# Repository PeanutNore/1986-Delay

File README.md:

# 1986-Delay
This program is distributed in the hope that it will be useful,
but WITHOUT ANY WARRANTY; without even the implied warranty of
MERCHANTABILITY or FITNESS FOR A PARTICULAR PURPOSE.

1986 Delay: A Stereo Digital Delay pedal for guitar built around the AVR128DA28 MCU.

Up to 1000 millisecond delay with stereo outputs and two modes

Mode 1: Ping-Pong delay. Output B has half the delay time of output A

Mode 2: "Reverse Ping-Pong" delay. Output A has half the selected delay time and runs like a stardard delay, while output B runs in reverse and is synchronized with output A for a stereo effect.

Digital Controls:

  A: Effective delay line length
  
  B: Sample rate

Analog Controls:

  Mix: The amount of delayed signal mixed with the dry signal at output
  
  Feedback: The amount of delayed signal mixed with the input signal to the delay line

 * Copyright 2025 Samuel Brown. All Rights Reservered.
 * 
 * Licensed under Creative Commons CC-BY-NC-SA 4.0
 * https://creativecommons.org/licenses/by-nc-sa/4.0/
 * 
 * You are free to share and adapt this software for non-
 * commercial purposes provided that you give appropriate 
 * credit and attribution, and distribute your contributions 
 * under the same CC-BY-NC-SA license.
 * 
 * For commercial licensing contact sam.brown.rit08@gmail.com

To use this software you will need:
* Arduino IDE version 1.8.19 or greater
* DxCore library for AVR128DA28 support (https://github.com/SpenceKonde/DxCore)
* Any USB to UPDI programmer. I recommend the Adafruit UPDI Friend because it is easy to use and under $20
* An AVR128DA28 MCU and appropriate supporting circuitry. Refer to the KiCad schematic and board files included in this repository.

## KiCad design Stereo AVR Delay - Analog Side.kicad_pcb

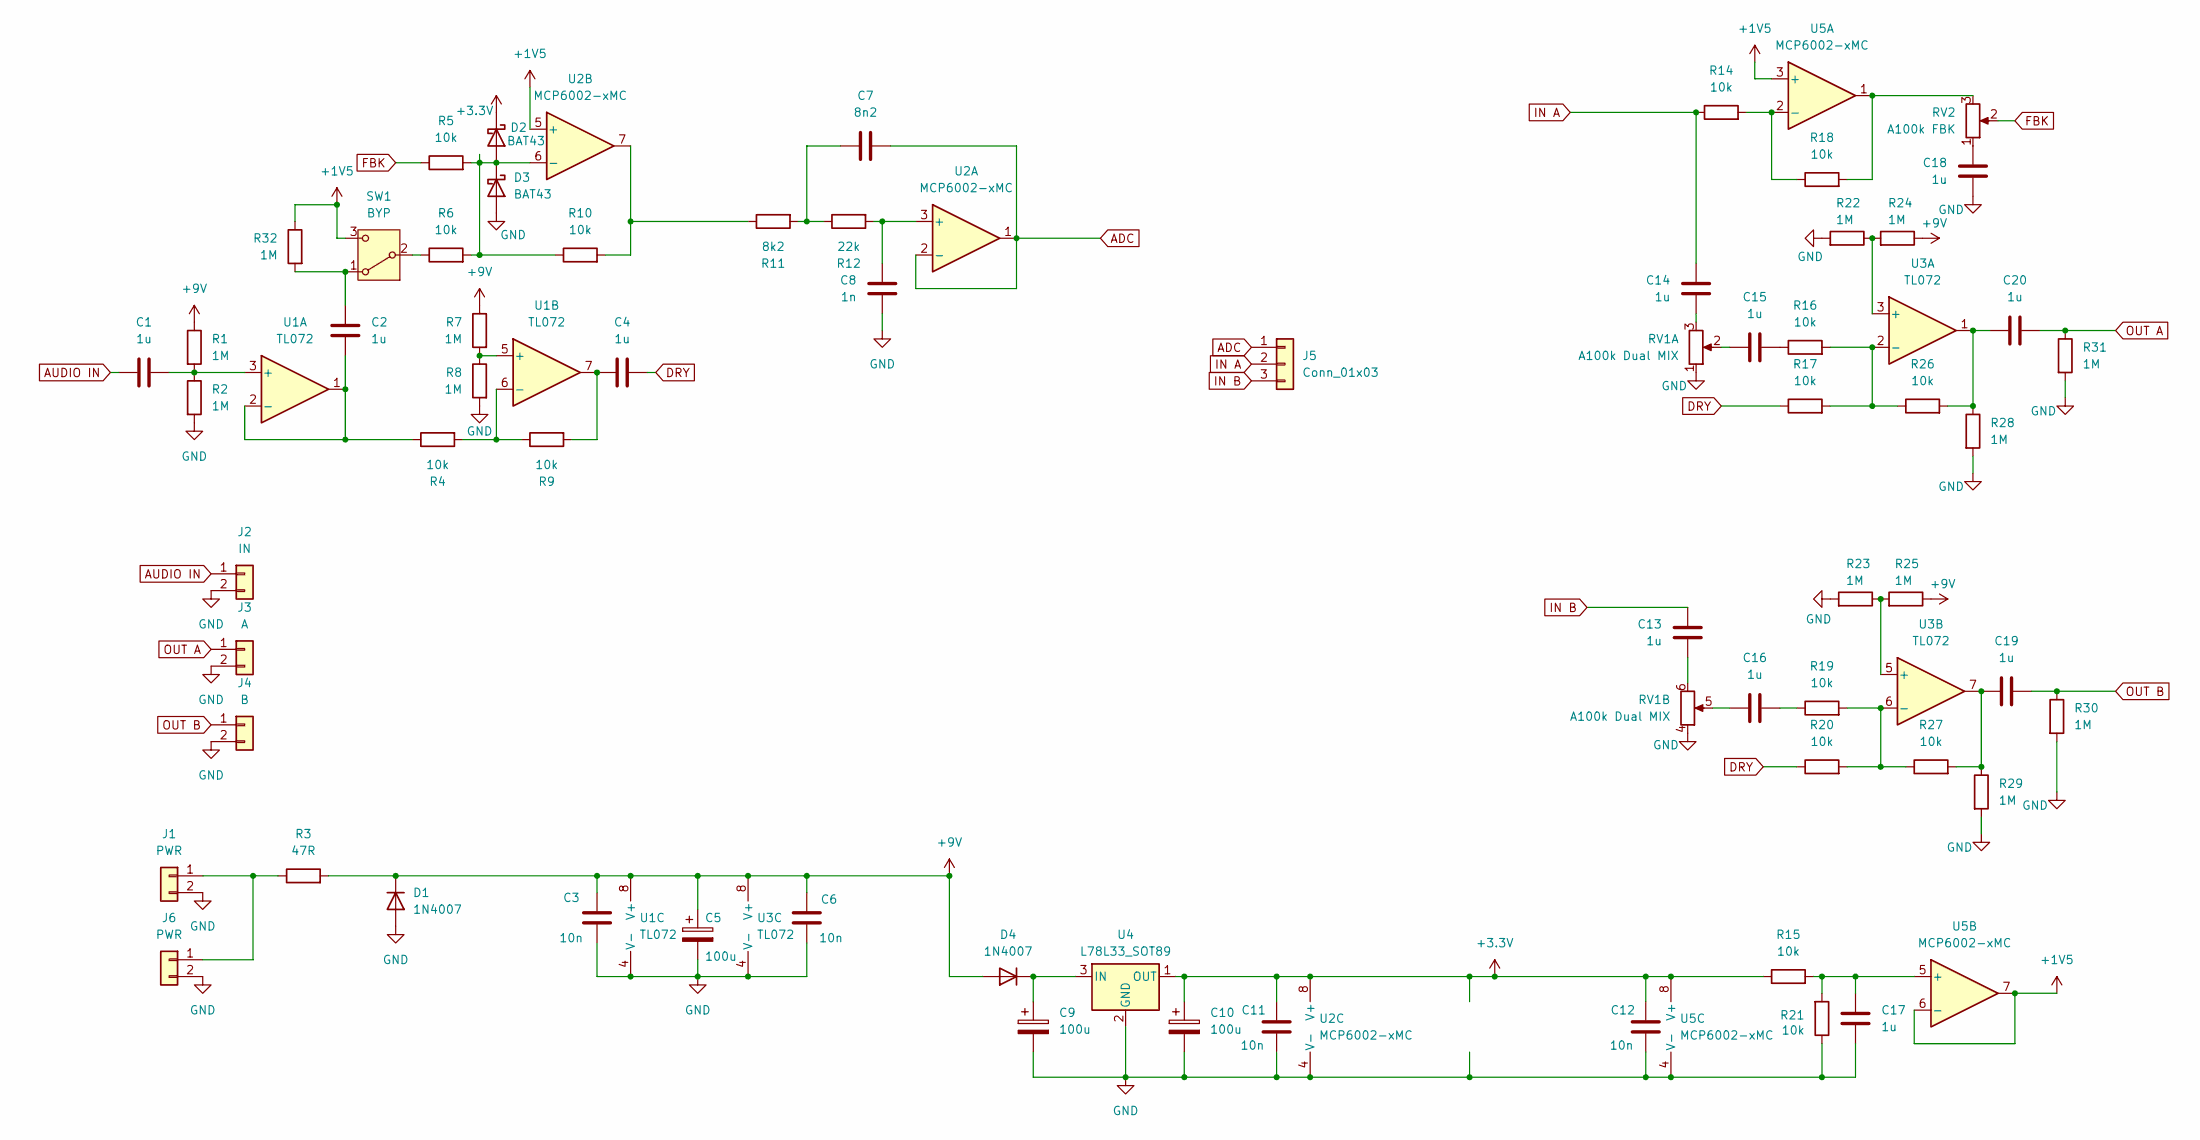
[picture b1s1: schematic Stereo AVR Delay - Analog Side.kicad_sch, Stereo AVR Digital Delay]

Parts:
C1, C2, C4, C13, C14, C15, C16, C17, C18, C19, C20: 1u; C_1206_3216Metric
C3, C6, C11, C12: 10n; C_0603_1608Metric
C5, C9, C10: 100u; CP_Radial_D6.3mm_P2.50mm
C7: 8n2; C_0603_1608Metric
C8: 1n; C_0603_1608Metric
D1, D4: 1N4007; D_DO-35_SOD27_P7.62mm_Horizontal
D2, D3: BAT43; D_DO-35_SOD27_P7.62mm_Horizontal
J1, J6: PWR; PinHeader_1x02_P2.54mm_Vertical
J2: IN; PinHeader_1x02_P2.54mm_Vertical
J3: A; PinHeader_1x02_P2.54mm_Vertical
J4: B; PinHeader_1x02_P2.54mm_Vertical
J5: Conn_01x03; PinHeader_1x03_P2.54mm_Vertical
R1, R2, R7, R8, R22, R23, R24, R25, R28, R29, R30, R31, R32: 1M; R_0805_2012Metric
R3: 47R; R_Axial_DIN0207_L6.3mm_D2.5mm_P7.62mm_Horizontal
R4, R5, R6, R9, R10, R14, R15, R16, R17, R18, R19, R20, R21, R26, R27: 10k; R_0805_2012Metric
R11: 8k2; R_0805_2012Metric
R12: 22k; R_0805_2012Metric
RV1: A100k Dual MIX; RV16A01F-41
RV2: A100k FBK; RV16AF-41
SW1: BYP; PinHeader_1x03_P2.54mm_Vertical
U1, U3: TL072; SOIC-8_3.9x4.9mm_P1.27mm
U2, U5: MCP6002-xMC; DIP-8_W7.62mm_Socket
U4: L78L33_SOT89; TO-92_Inline_Wide

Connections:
+1V5: R32.1, SW1.3 (C), U2.5 (+), U5.3 (+), U5.6 (-), U5.7
+3.3V: C10.1, C11.1, C12.1, D2.1 (K), R15.1, U2.8 (V+), U4.1 (OUT), U5.8 (V+)
+9V: C3.1, C5.1, C6.1, D1.1 (K), D4.2 (A), R1.1, R3.2, R7.1, R24.1, R25.1, U1.8 (V+), U3.8 (V+)
ADC: C7.2, J5.1, U2.1, U2.2 (-)
AUDIO IN: C1.1, J2.1
DRY: C4.2, R17.1, R20.1
FBK: R5.1, RV2.2
GND: C3.2, C5.2, C6.2, C8.1, C9.2, C10.2, C11.2, C12.2, C17.1, C18.1, D1.2 (A), D3.2 (A), J1.2, J2.2, J3.2, J4.2, J6.2, R2.2, R8.2, R21.1, R22.2, R23.2, R28.2, R29.2, R30.2, R31.2, RV1.1, RV1.4, U1.4 (V-), U2.4 (V-), U3.4 (V-), U4.2 (GND), U5.4 (V-)
IN A: C14.2, J5.2, R14.1
IN B: C13.2, J5.3
unnamed: C4.1, R9.2, U1.7
unnamed: C7.1, R11.2, R12.1
unnamed: C13.1, RV1.6
unnamed: C14.1, RV1.3
unnamed: C15.1, RV1.2
unnamed: C15.2, R16.1
unnamed: C16.1, RV1.5
unnamed: C16.2, R19.1
unnamed: C18.2, RV2.1
unnamed: C19.1, R27.2, R29.1, U3.7
unnamed: C20.1, R26.2, R28.1, U3.1
unnamed: D2.2 (A), D3.1 (K), R5.2, R6.2, R10.1, U2.6 (-)
unnamed: C9.1, D4.1 (K), U4.3 (IN)
unnamed: J1.1, J6.1, R3.1
unnamed: R10.2, R11.1, U2.7
unnamed: R18.2, RV2.3, U5.1
unnamed: C2.2, R32.2, SW1.1 (A)
unnamed: R6.1, SW1.2 (B)
unnamed: C1.2, R1.2, R2.1, U1.3 (+)
unnamed: C2.1, R4.1, U1.1, U1.2 (-)
unnamed: R7.2, R8.1, U1.5 (+)
unnamed: R4.2, R9.1, U1.6 (-)
unnamed: C8.2, R12.2, U2.3 (+)
unnamed: R22.1, R24.2, U3.3 (+)
unnamed: R16.2, R17.2, R26.1, U3.2 (-)
unnamed: R23.1, R25.2, U3.5 (+)
unnamed: R19.2, R20.2, R27.1, U3.6 (-)
unnamed: R14.2, R18.1, U5.2 (-)
unnamed: C17.2, R15.2, R21.2, U5.5 (+)
OUT A: C20.2, J3.1, R31.1
OUT B: C19.2, J4.1, R30.1

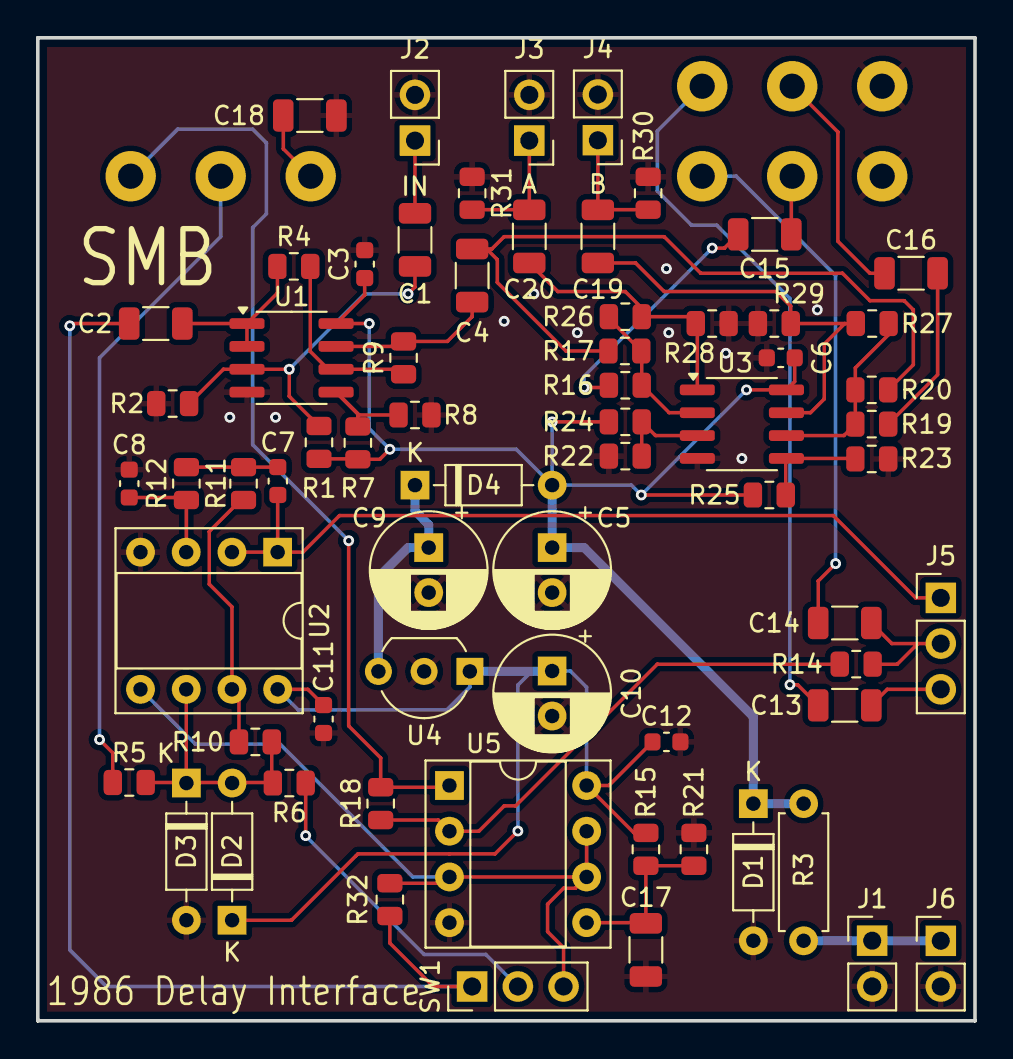
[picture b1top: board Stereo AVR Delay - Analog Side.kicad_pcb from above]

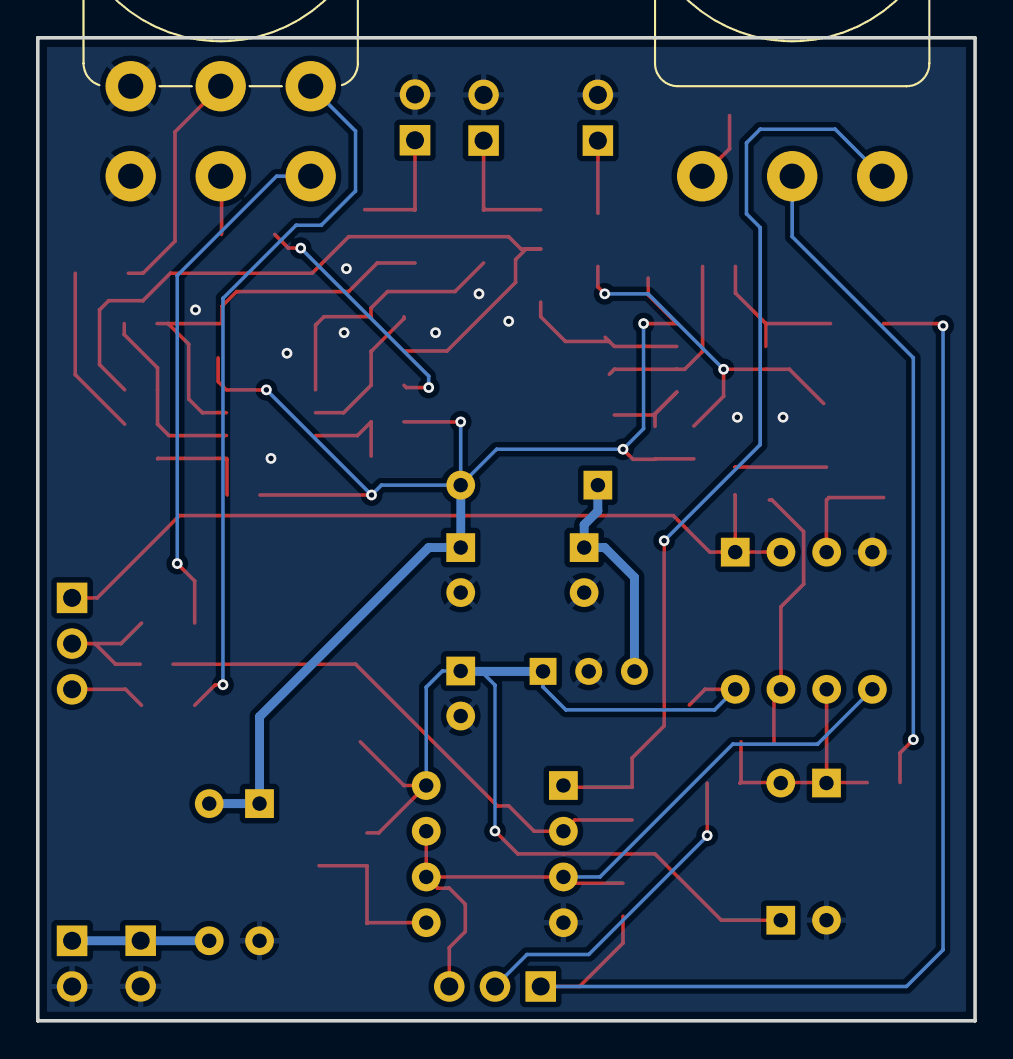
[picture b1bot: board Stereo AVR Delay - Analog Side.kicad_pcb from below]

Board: 2 copper layers, 52.1 x 54.6 mm, 69 parts (2 on the bottom side), 41 nets.

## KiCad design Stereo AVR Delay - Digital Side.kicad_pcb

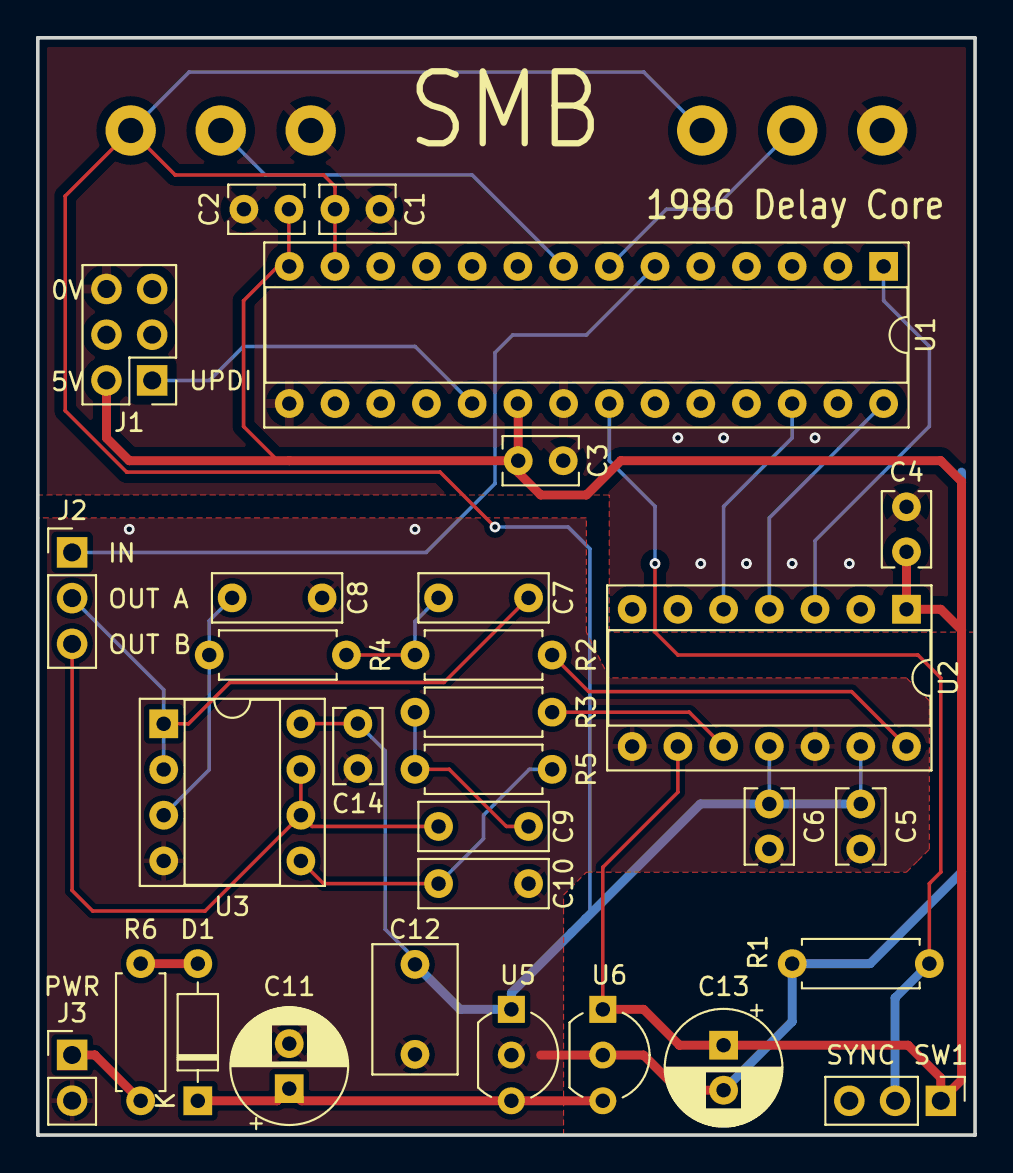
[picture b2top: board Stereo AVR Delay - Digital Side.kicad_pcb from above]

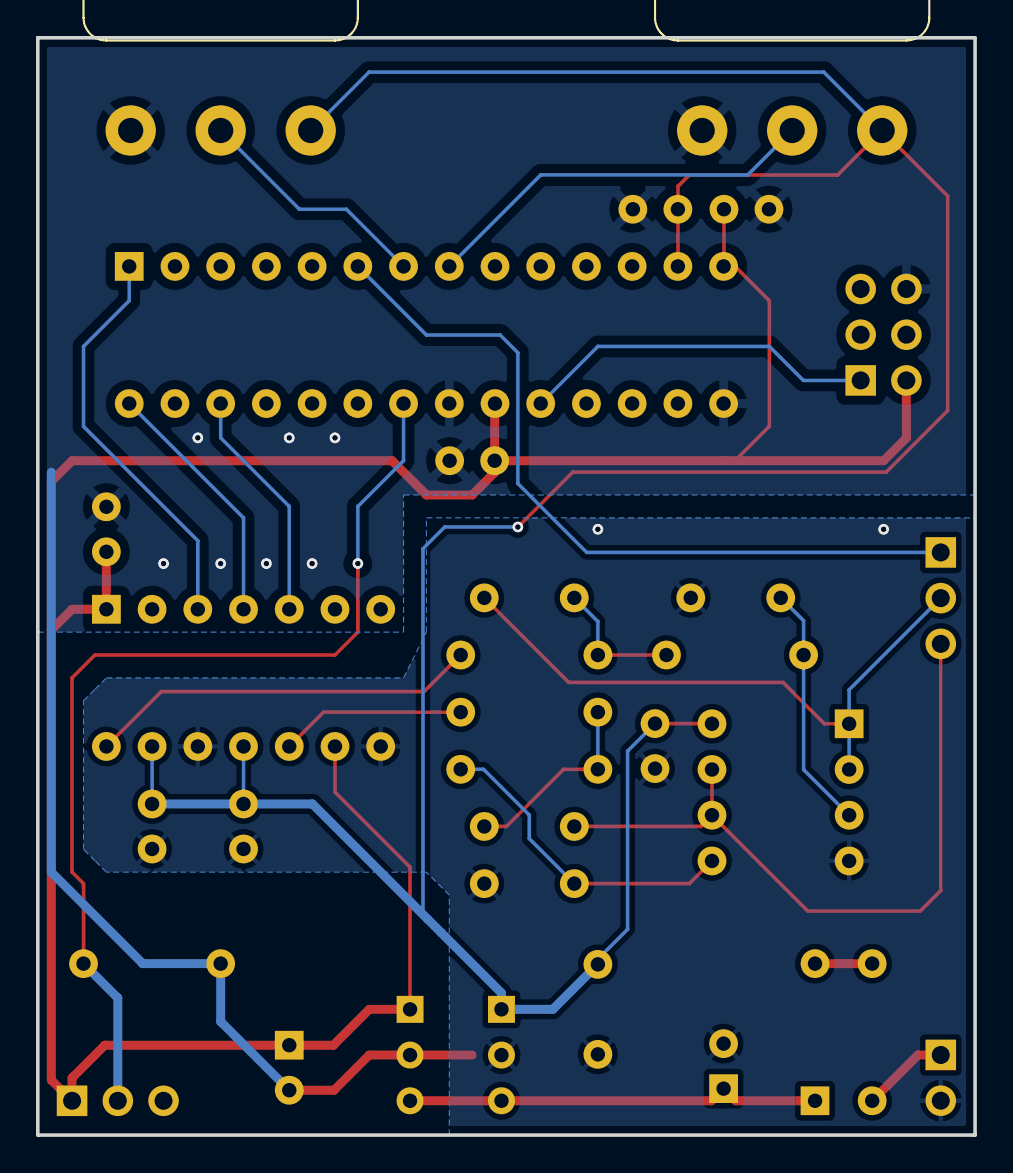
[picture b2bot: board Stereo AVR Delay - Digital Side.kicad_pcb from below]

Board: 2 copper layers, 52.1 x 61.0 mm, 32 parts (2 on the bottom side), 22 nets.

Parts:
C1, C2, C3, C4, C5, C6, C14: 10n; C_Rect_L4.0mm_W2.5mm_P2.50mm
C7, C9: 10n; C_Rect_L7.0mm_W2.5mm_P5.00mm
C8, C10: 1n2; C_Rect_L7.0mm_W2.5mm_P5.00mm
C11, C13: 100u; CP_Radial_D6.3mm_P2.50mm
C12: 1u; C_Rect_L7.0mm_W4.5mm_P5.00mm
D1: 1N4007; D_DO-35_SOD27_P7.62mm_Horizontal
J1: UPDI; PinHeader_2x03_P2.54mm_Vertical
J2: Conn_01x03; PinHeader_1x03_P2.54mm_Vertical
J3: PWR; PinHeader_1x02_P2.54mm_Vertical
R1, R4, R5: 22k; R_Axial_DIN0207_L6.3mm_D2.5mm_P7.62mm_Horizontal
R2, R3: 9k1; R_Axial_DIN0207_L6.3mm_D2.5mm_P7.62mm_Horizontal
R6: 47R; R_Axial_DIN0207_L6.3mm_D2.5mm_P7.62mm_Horizontal
RV1: 25k Delay Time A; RV16AF-41
RV2: 25k Delay Time B; RV16AF-41
SW1: SYNC; PinHeader_1x03_P2.54mm_Vertical
U1: AVR128DA28; DIP-28_W7.62mm_Socket
U2: MCP4922; DIP-14_W7.62mm_Socket
U3: MCP6002-xMC; DIP-8_W7.62mm_Socket
U5: L78L33; TO-92_Inline_Wide
U6: L78L05; TO-92_Inline_Wide

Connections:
+3.3V: C1.2, C5.1, C6.1, C12.1, C14.2, RV1.3, RV2.3, U1.13 (VREFA/PD7), U2.11 (VrefB), U2.13 (VrefA), U3.8 (V+), U5.1 (OUT)
+5V: C2.2, C3.1, C4.2, C13.1, J1.2 (VCC), SW1.1 (A), U1.14 (AVDD), U1.20 (VDD), U2.1 (VDD), U2.9 (~SHDN), U6.1 (OUT)
ADC IN: J2.1, U1.6 (PD0)
GND: C1.1, C2.1, C3.2, C4.1, C5.2, C6.2, C8.1, C10.1, C11.2, C12.2, C13.2, C14.1, J1.6 (GND), J3.2, R1.2, RV1.1, RV2.1, U1.15 (GND), U1.21 (GND), U2.8 (~LDAC), U2.12 (AVSS), U3.4 (V-), U5.2 (GND), U6.2 (GND)
unnamed: C7.1, R2.2, R4.1
unnamed: C9.1, R3.2, R5.1
unnamed: D1.2 (A), R6.2
unnamed: C11.1, D1.1 (K), U5.3 (IN), U6.3 (IN)
unnamed: J1.1 (DATA), U1.19 (UPDI)
unnamed: J3.1, R6.1
unnamed: R1.1, SW1.2 (B), U1.22 (PA0)
unnamed: U1.26 (PA4), U2.5 (SDI)
unnamed: U1.28 (PA6), U2.4 (SCK)
unnamed: U1.1 (PA7), U2.3 (~CS)
unnamed: RV1.2, U1.7 (PD1)
unnamed: RV2.2, U1.8 (PD2)
unnamed: R2.1, U2.14 (VoutA)
unnamed: R3.1, U2.10 (VoutB)
unnamed: C8.2, R4.2, U3.3 (+)
unnamed: C10.2, R5.2, U3.5 (+)
OUT A: C7.2, J2.2, U3.1, U3.2 (-)
OUT B: C9.2, J2.3, U3.6 (-), U3.7

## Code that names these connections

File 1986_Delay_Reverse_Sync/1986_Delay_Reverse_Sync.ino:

/* 1986 Delay
 * Stereo Digital Delay Pedal for Guitar
 * High resolution version with half delay time - reads and stores full 12 bit samples in delay array
 * Version 1.2
 * 
 * Requries the following libraries:
 * DxCore - https://github.com/SpenceKonde/DxCore - install via Boards Manager in Arduino IDE
 * 
 * Removed requirement for MCP_DAC library - now calls SPI functions directly
 * 
 * For AVR512DA28 microcontrollers
 * 
 * Copyright 2025 Samuel Brown. All Rights Reservered.
 * 
 * Licensed under Creative Commons CC-BY-NC-SA 4.0
 * https://creativecommons.org/licenses/by-nc-sa/4.0/
 * 
 * You are free to share and adapt this software for non-
 * commercial purposes provided that you give appropriate 
 * credit and attribution, and distribute your contributions 
 * under the same CC-BY-NC-SA license.
 * 
 * For commercial licensing contact sam.brown.rit08@gmail.com
 */

#include "SPI.h"


//IO Pins
const uint8_t InputPin = PIN_PD0;
const uint8_t TimePinA = PIN_PD1;
const uint8_t TimePinB = PIN_PD2;
const uint8_t SyncPin = PIN_PA0;
const uint8_t DAC_CS = PIN_PA7;
//Audio Samples
volatile uint16_t sampleIn;
volatile uint16_t sampleOutA;
volatile uint16_t sampleOutB;
volatile uint16_t delayArray[8000];
//Step Counters
volatile uint16_t sampleStep = 0;
volatile int16_t delayStepA = 0;
volatile int16_t delayStepB = 0;
//Controls
volatile uint16_t delayTimeA = 0;
volatile uint16_t targetTimeA = 0;
volatile uint16_t delayTimeB = 0;
volatile uint16_t targetTimeB = 0;
volatile uint16_t extraClocks = 0;
volatile bool resetSample = false;

uint32_t _SPIspeed = 20000000;
SPISettings _spi_settings;

ISR(TCA0_OVF_vect) {                                        //runs each time the TCA0 periodic interrupt triggers
  TCA0.SINGLE.INTFLAGS = TCA_SINGLE_OVF_bm;                 //clear the interrupt flags

  //analogSampleDuration(0);
  sampleIn = analogRead(InputPin);                          //read the audio input
  //ADC0.MUXPOS = ((TimePinA & 0x7F) << ADC_MUXPOS_gp);
  
  //analogSampleDuration(4);
  targetTimeA = analogRead(TimePinA) >> 3;                   //read the delay time A knob as a value from 0-511 to reduce noise
  targetTimeA *= 15;                                         //scale it to 0-7665
  targetTimeA += 335;                                        //shift it so it maxes out at 8000
  if (delayTimeA < targetTimeA){delayTimeA++;}
  if (delayTimeA > targetTimeA){delayTimeA--;}
  delayTimeB = delayTimeA >> 1;                             //set delay time B to half of delay time 

  extraClocks = analogRead(TimePinB) >> 1;
  TCA0.SINGLE.PERBUF = 1200 + extraClocks;

  //reverse ping pong mode
  if (digitalReadFast(SyncPin)){
    delayStepA = sampleStep - delayTimeB;
    if (delayStepA < 0){delayStepA += delayTimeA;}
    delayStepB--;
    if (delayStepB < 0){delayStepB = delayTimeA;}
    if (sampleStep == (delayTimeA - 1)){resetSample = true;}
  }

  //default mode: ping pong
  else {
    delayStepA = sampleStep - delayTimeA;
    if (delayStepA < 0){delayStepA += 8000;}
    delayStepB = sampleStep - delayTimeB;
    if (delayStepB < 0){delayStepB += 8000;}
  }

  ADC0.MUXPOS = ((InputPin & 0x7F) << ADC_MUXPOS_gp);
  
  //output the delayed samples via external DAC
  //prepare and output A:
  sampleOutA = delayArray[delayStepA];        //get the sample at step A
  sampleOutA |= 0x3000;                       //add the command bits for the DAC (channel 0)
  digitalWriteFast(DAC_CS, LOW);
  SPI.beginTransaction(_spi_settings);
  SPI.transfer((uint8_t)(sampleOutA >> 8));   //send the high byte first
  SPI.transfer((uint8_t)(sampleOutA & 0xFF)); //send the low byte second
  SPI.endTransaction();
  digitalWriteFast(DAC_CS, HIGH);
  //prepare and output B:
  sampleOutB = delayArray[delayStepB];        //get the sample at step B
  sampleOutB |= 0xB000;                       //add the command bits for the DAC (channel 1)
  digitalWriteFast(DAC_CS, LOW);
  SPI.beginTransaction(_spi_settings);
  SPI.transfer((uint8_t)(sampleOutB >> 8));   //send the high byte first
  SPI.transfer((uint8_t)(sampleOutB & 0xFF)); //send the low byte second
  SPI.endTransaction();
  digitalWriteFast(DAC_CS, HIGH);
  
  //re-read the input and average it with earlier reading and store it
  //analogSampleDuration(0);
  sampleIn += analogRead(InputPin);                         //read the audio input again and add it to the previous
  sampleIn = sampleIn >> 1;                                 //divide by 2 to get the average (reduce quantization noise)
  delayArray[sampleStep] = sampleIn;                        //store the input in the delay line
  
  //increment the step counter and roll over to 0 after the last position
  sampleStep++;
  if ((sampleStep > 7999) || resetSample){
    sampleStep = 0;
    delayStepB = delayTimeA;           //the record and reverse playback heads need to be rolled over together for this to work right
    resetSample = false;
  }
}

void setup() {
  //fill the delay array with silence
  for (int i = 0; i < 8000; i++){
    delayArray[i] = 2047;
  }
  //setup I/O
  SPI.begin();
  pinMode(InputPin, INPUT);
  pinMode(TimePinA, INPUT);
  pinMode(TimePinB, INPUT);
  pinMode(SyncPin, INPUT);
  pinMode(DAC_CS, OUTPUT);
  digitalWriteFast(DAC_CS, HIGH);
  _spi_settings = SPISettings(_SPIspeed, MSBFIRST, SPI_MODE0);
  //setup ADC
  analogReference(EXTERNAL);
  analogReadResolution(12);
  analogSampleDuration(0);
  analogClockSpeed(2000);
  //get starting control settings
  delayTimeA = analogRead(TimePinA) << 1;                   //read the delay time A knob as a value from 0-8191
  delayTimeA++;
  if (delayTimeA > 8000){delayTimeA = 8000;}
  delayTimeB = delayTimeA >> 1;                           //set delay time B to half of delay time 
  delayStepB = delayTimeA - 1;
  ADC0.MUXPOS = ((InputPin & 0x7F) << ADC_MUXPOS_gp);
  //setup interrupt timing for desired sample rate
  takeOverTCA0();
  TCA0.SINGLE.INTFLAGS = TCA_SINGLE_OVF_bm;
  TCA0.SINGLE.INTCTRL  = 0b00000001;                // overflow interrupt every PER cycles
  TCA0.SINGLE.CTRLA    = TCA_SINGLE_CLKSEL_DIV1_gc; // Clock prescaler / 1 (24 MHz)    
  TCA0.SINGLE.PER      = 1200;                      // ADJUST SAMPLE RATE HERE - 1000 clocks = 24ksps , 1200 clocks = 20ksps, 1500 clocks = 16ksps - ADJUST SAMPLE RATE HERE
  TCA0.SINGLE.CTRLA   |= 1;                         // Enables the timer
}

void loop() {
  // put your main code here, to run repeatedly:

}

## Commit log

2025-03-21 Add CC license info
2025-03-21 Added main source code
2025-03-21 Added KiCad files
2025-03-21 Updated formatting & comments
2025-03-24 Optimizations for higher sample rate
2025-03-25 Removed dependency of MCP_DAC library
2025-03-25 Removed dependency on MCP_DAC library
2025-03-25 Fixed typo in comments
2025-05-02 Noise reduction
